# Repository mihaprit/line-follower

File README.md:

# line-follower
Design and develeopment of a line-follower robot for a school project.

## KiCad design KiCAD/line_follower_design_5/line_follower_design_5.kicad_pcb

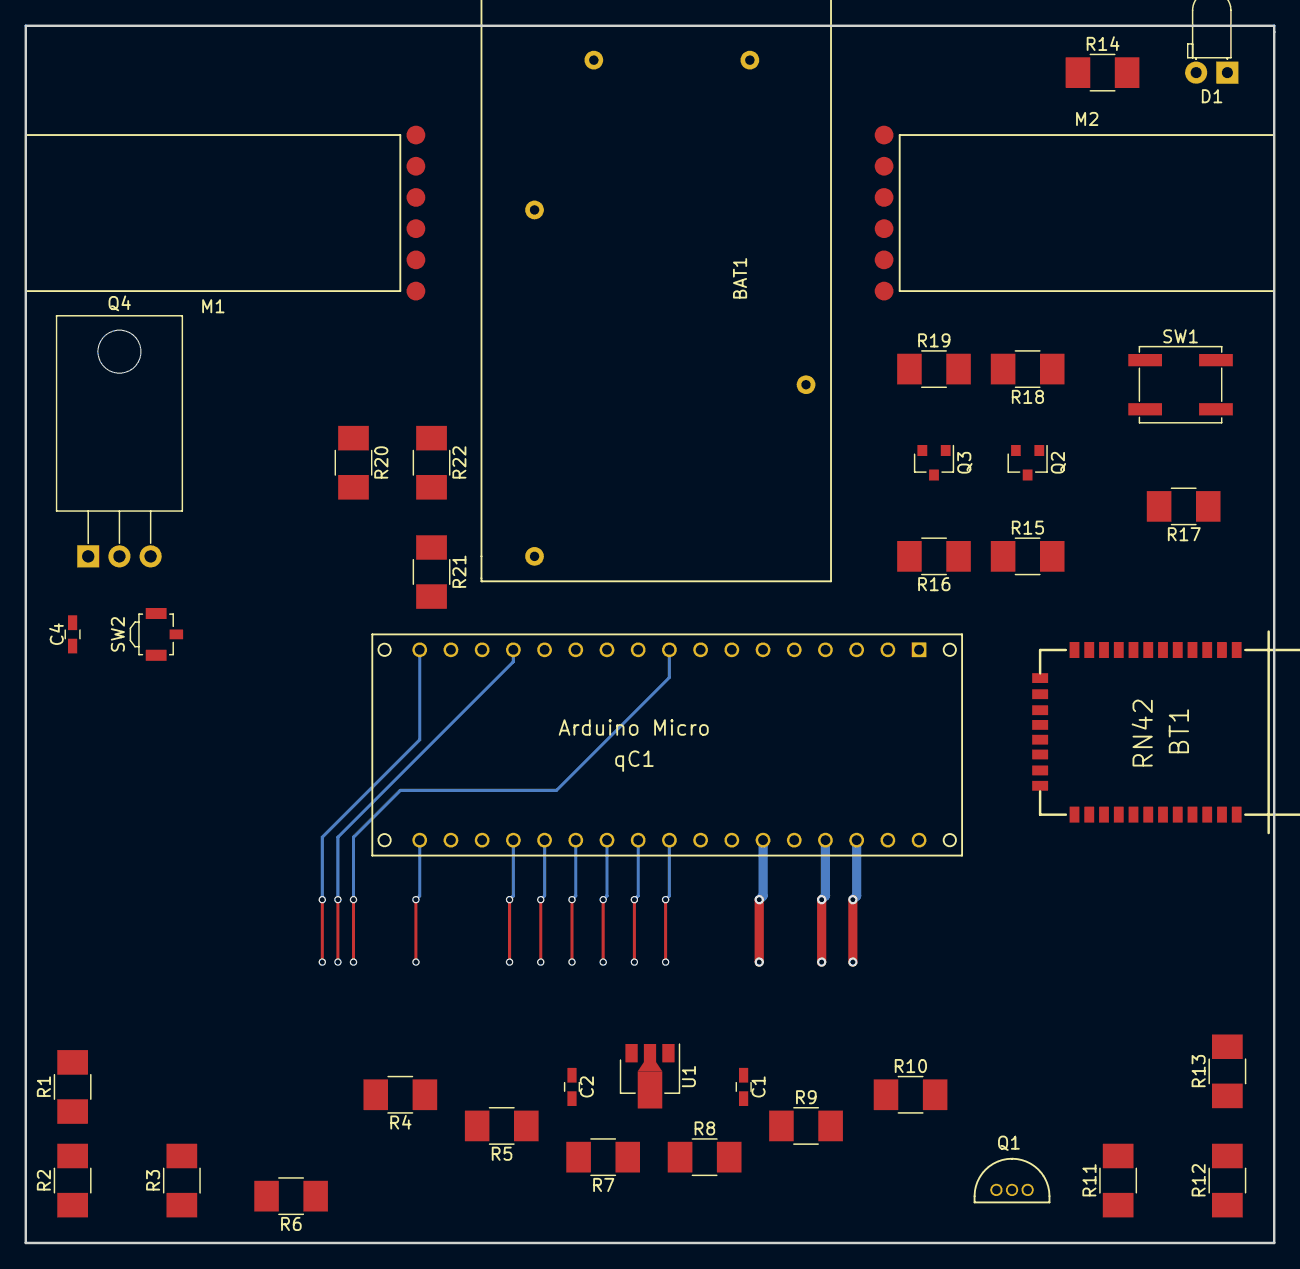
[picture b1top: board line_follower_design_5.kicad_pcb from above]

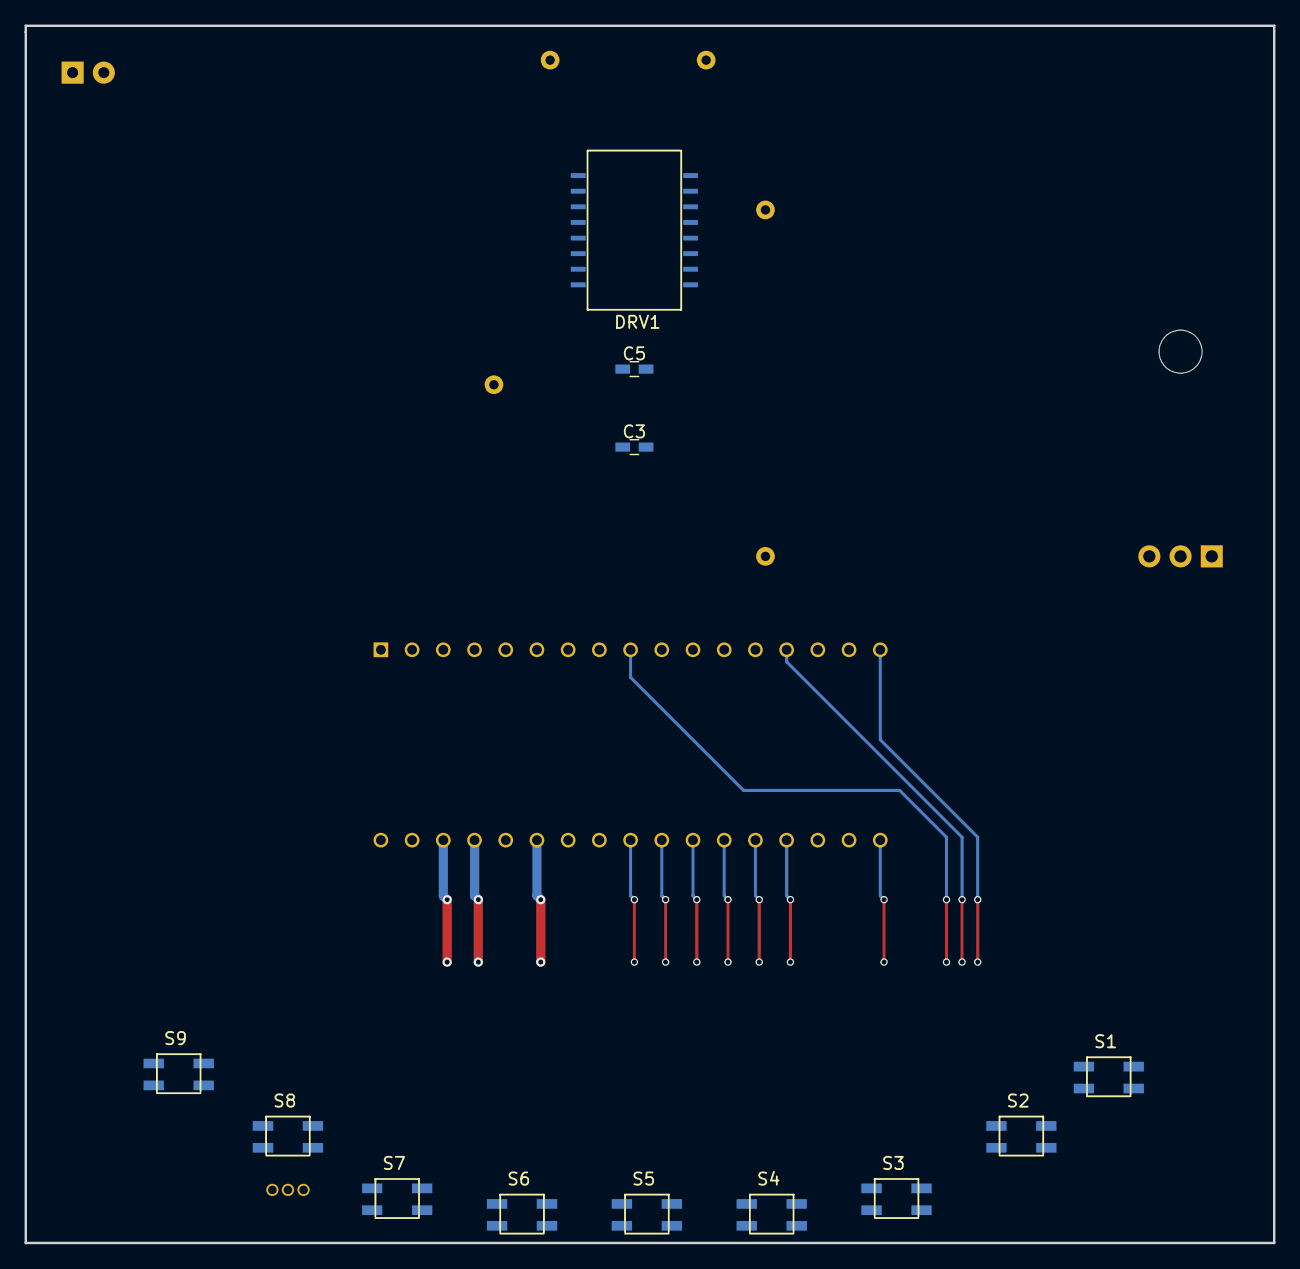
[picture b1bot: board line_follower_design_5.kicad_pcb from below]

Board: 2 copper layers, 101.6 x 99.1 mm, 50 parts (12 on the bottom side), 47 nets.

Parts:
BAT1: Baterija; 12BH611-GR
BT1: RN42; rn42footprint
C1, C2: 1uF; C_0603_HandSoldering
C3: CM1; C_0603_HandSoldering
C4: 22uF; C_0603_HandSoldering
C5: CM2; C_0603_HandSoldering
D1: LED; LED_D3.0mm_Horizontal_O1.27mm_Z2.0mm
DRV1: L293; L293D
M1: Motor Levi; HPCB Motor (Pololu)
M2: Motor Desni; HPCB Motor (Pololu)
Q1: Q_NPN_BCE; BCE547B(T0-92)
Q2, Q3: BSS138; SOT-23
Q4: Q_PMOS_GDS; TO-220_Horizontal
R1, R5, R10: 10; R_1210_HandSoldering
R2, R3, R4, R7, R8, R9, R11, R12, R13, R17, R20, R21, R22: 10K; R_1210_HandSoldering
R6: 1K; R_1210_HandSoldering
R14: 470R; R_1210_HandSoldering
R15, R16, R18, R19: R10K; R_1210_HandSoldering
S1, S2, S3, S4, S5, S6, S7, S8, S9: QRE1113
SW1: switch_psh; SW_SPST_EVQP0
SW2: switch; SW_SPST_B3U-3100P
U1: MCP1703A-5002/MB; SOT89-3_Housing
qC1: Arduino Micro; ARDUINO_MICRO_SHIELD

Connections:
+3V3: BT1.11, Q2.1, Q3.1, R18.1, R19.1, qC1.19
+5V: DRV1.1, DRV1.9, DRV1.16, M1.3, M2.3, R2.1, R3.1, R4.1, R7.1, R8.1, R9.1, R11.1, R12.1, R13.1, R15.1, R16.1, R17.1, qC1.29
+9V: C1.1, DRV1.8, Q4.3, R21.1, U1.2, qC1.32
+9VA: BAT1.1, C4.1, Q4.2, R20.1, SW2.1
/BTRX: BT1.14, Q2.3, R15.2, R19.2, qC1.1
/BTTX: BT1.13, Q2.2, Q3.3, R16.2, R18.2, qC1.2
/BUT: R17.2, SW1.1, qC1.12
/ENCLA: M1.5, qC1.3
/ENCLB: M1.4, qC1.4
/ENCRA: M2.4, qC1.7
/ENCRB: M2.5, qC1.8
/LED: R14.1, qC1.34
/LON: R6.2, qC1.18
/LS1: R2.2, S1.3, qC1.9
/LS2: R3.2, S2.3, qC1.14
/LS3: R4.2, S3.3, qC1.17
/LS4: R7.2, S4.3, qC1.21
/LS5: R8.2, S5.3, qC1.22
/LS6: R9.2, qC1.23
/LS7: R11.2, S7.3, qC1.24
/LS8: R12.2, S8.3, qC1.25
/LS9: R13.2, S9.3, qC1.26
/PWML1: DRV1.2, qC1.10
/PWML2: DRV1.7, qC1.11
/PWMR1: DRV1.10, qC1.15
/PWMR2: DRV1.15, qC1.16
/VBAT: R21.2, R22.1, qC1.13
GND: BT1.1, BT1.12, BT1.28, BT1.29, C1.2, C2.2, D1.1, DRV1.4, DRV1.5, DRV1.12, DRV1.13, M1.6, M2.6, Q1.3, R22.2, S1.4, S2.4, S3.4, S4.4, S5.4, S6.4, S7.4, S8.4, S9.4, SW1.2, U1.1, qC1.6, qC1.31
unnamed: BAT1.2, C4.2, SW2.3
unnamed: C2.1, R1.1, R5.1, R10.1, U1.3
unnamed: C3.1, DRV1.3, M1.1
unnamed: C3.2, DRV1.6, M1.2
unnamed: C5.1, DRV1.14, M2.1
unnamed: C5.2, DRV1.11, M2.2
unnamed: D1.2, R14.2
unnamed: Q1.1, R6.1
unnamed: Q1.2, S3.2, S6.2, S9.2
unnamed: Q4.1, R20.2, SW2.2
unnamed: R1.2, S1.1
unnamed: R5.2, S4.1
unnamed: R10.2, S7.1
unnamed: S1.2, S2.1
unnamed: S2.2, S3.1
unnamed: S4.2, S5.1
unnamed: S5.2, S6.1
unnamed: S7.2, S8.1
unnamed: S8.2, S9.1

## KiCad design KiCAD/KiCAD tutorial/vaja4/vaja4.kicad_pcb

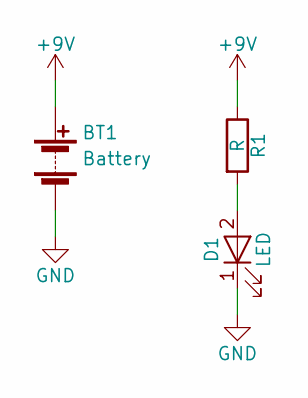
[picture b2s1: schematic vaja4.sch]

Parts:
BT1: Battery; R_0805_HandSoldering
D1: LED; LED_0805
R1: R; TerminalBlock_Pheonix_MPT-2.54mm_2pol

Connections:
+9V: BT1.1 (+), R1.1
GND: BT1.2 (-), D1.1 (K)
unnamed: D1.2 (A), R1.2

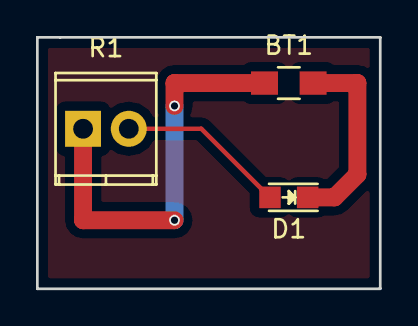
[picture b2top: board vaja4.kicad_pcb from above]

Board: 2 copper layers, 19.1 x 14.0 mm, 3 parts (0 on the bottom side), 3 nets.

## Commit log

2017-03-09 KiCAD Tutorials & design no. 1
    Tutorials files for learning KiCAD,; map "tutorial" and an unfinished
    schematic for the circuit on the design no. 1 of the line-follower
    robot; line_follower_design_1
2017-03-12 line-follower-design-2 shema
    9 senzorjev, regulator napetosti, 2 npn tranzistorja, rn42, brez mux-a.
2017-03-13 Cleanup of duplicate files
    Deletion of duplicate files
2017-03-13 Shematic moved into a shematic folder.
    Line follower design 2 shematic moved into a shematic folder.
2017-03-15 Vaja 4 Tutorial for KiCAD
    PCB line drawing tutorial files for KiCAD.
2017-03-15 line follower design 3
    Added 2 level shifters for communication from and to Arduino to BT (5 -
    3.3V level shifter). Second one is redundant for safety.
2017-03-17 MOSFET Datasheet
    Added link for NMOSFET and datasheet.
2017-03-17 Datasheets PMOS
    Components datasheet updating.
2017-03-23 Vaja 5
    KiCAD tutorial files from exercise nu. 5.
2017-03-23 line-follower-design-4
    A new design. All sensors now on analog pins. Synchronized sensors now
    with one maser LON transistor. A speaker removed and replaced with LED
    and a resistor (smaller footprint, lighter).
2017-03-23 Library dependencies fix.
    Fixing library dependencies for older versions of the project.
2017-03-23 Arduino Micro Footprint
    Added a footprint folder and an Arduino Micro footprint.
2017-03-25 Files
    Datasheets, 3D models and FreeRoute
2017-03-25 Footprints updates
    Footprints files for Arduino Micro, Motor, L293D, QRE1113 and RN42.
2017-03-25 line-follower-design 4 updates
    Shematic updates, library updates, netlist, unrouted PCB layout (1st
    iteration).
2017-03-25 line-follower-design-4 PCB and Routing
    PCB and routing files for design. no. 4. First finished iteration. Some
    clearance issues.
2017-03-26 Footprint NPN transistor
    Footprint for BCE547B(T0-92) NPN transistor
2017-03-26 line-follower-design-4 schematic update, pcb update
    Library dependencies update, PCB components optimizations.
2017-03-26 line-follower-design-5
    A new design, schematic identical to design 4. New PCB layout. Bridge
    concept. No route optimizations.
